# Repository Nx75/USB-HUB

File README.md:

# USB-HUB

## Schematics

## Boardview

## 3d view 

## NOTE : MADE IN EASYEDA

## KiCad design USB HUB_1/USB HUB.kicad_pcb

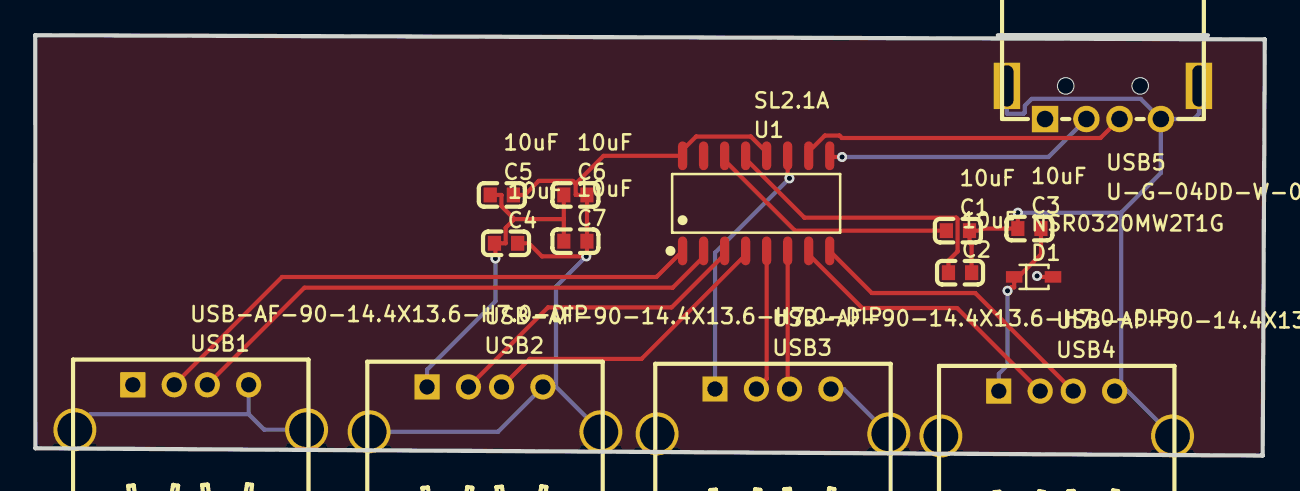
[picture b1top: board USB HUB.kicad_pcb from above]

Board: 4 copper layers, 74.3 x 25.4 mm, 14 parts (0 on the bottom side), 15 nets.

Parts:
C1, C2, C3, C4, C5, C6, C7: 10uF; C0603
D1: NSR0320MW2T1G; SOD-323_L1.8-W1.3-LS2.5-RD
U1: SL2.1A; SOP-16_L10.0-W3.9-P1.27-LS6.0-BL
USB1, USB2, USB3, USB4: USB-AF-90-14.4X13.6-H7.0-DIP; USB-A-TH_C46407
USB5: U-G-04DD-W-01; USB-A-TH_U-G-04WD-W-01

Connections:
+5V: C3.2, C4.1, C5.1, C6.1, C7.1, D1.1, U1.11, USB1.1, USB2.1, USB3.1, USB4.1
GND: C1.2, C2.2, C3.1, C4.2, C5.2, C6.2, C7.2, U1.12, U1.16, USB1.4, USB1.5, USB1.6, USB2.4, USB2.5, USB2.6, USB3.4, USB3.5, USB3.6, USB4.4, USB4.5, USB4.6, USB5.4, USB5.5, USB5.6
U1_1: U1.1, USB1.2
U1_2: U1.2, USB1.3
U1_3: U1.3, USB2.2
U1_4: U1.4, USB2.3
U1_5: U1.5, USB3.2
U1_6: U1.6, USB3.3
U1_7: U1.7, USB4.2
U1_8: U1.8, USB4.3
U1_9: U1.9, USB5.2
U1_10: U1.10, USB5.3
U1_13: C2.1, U1.13
U1_14: C1.1, U1.14
USB5_1: D1.2, USB5.1

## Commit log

2026-04-19 Add new boardview and 3D view images to README
2026-04-20 KICAD CONVERTED PROJECTS FILES
